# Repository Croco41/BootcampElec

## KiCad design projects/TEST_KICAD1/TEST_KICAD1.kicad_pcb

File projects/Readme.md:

# cgranja-piscineElec-design – Carte type Pro Mini (ATmega328P)

Petite carte basée sur un **ATmega328P-AU 16 MHz** 

---

## 1. Nomenclature (BOM)

| Référence | Qté | Valeur | Manufacture Part Number | Description | Caracteristiques | Empreinte |
| --- | --- | --- | --- | --- | --- | --- |
| C1,C2 | 2 | 12pF | CL10C120JB8NNNC | Unpolarized capacitor | 50V 12pF C0G ±5% 0603 Ceramic Capacitors RoHS | MyLibraryFootprint:MLF-CapacitorResistor-0603-1608mm |
| C3,C4,C5 | 3 | 100nF | CC0603KRX7R9BB104 | Unpolarized capacitor | 50V 100nF X7R ±10% 0603 Ceramic Capacitors RoHS | MyLibraryFootprint:MLF-CapacitorResistor-0603-1608mm |
| C6 | 1 | 1uF | CL10A105KB8NNNC | Unpolarized capacitor | 50V 1uF X5R ±10% 0603 Ceramic Capacitors RoHS | MyLibraryFootprint:MLF-CapacitorResistor-0603-1608mm |
| D1 | 1 | Green | TZ-P2-0603YGTCS1-0.6T | Light eminiting diode | 20mA 50mcd 570nm~575nm Yellow Green 1.9V~2.4V 60mW 0603 LED Indication - Discrete RoHS | MyLibraryFootprint:MLF-LED-0603-1608mm |
| D2 | 1 | Red | XL-1608SURC-06 | Light eminiting diode | 20mA 225mcd op View Mount 620nm~630nm Red 2.3V 50mW 0603 LED Indication - Discrete RoHS | MyLibraryFootprint:MLF-LED-0603-1608mm |
| J1 | 1 | ~ | | Header 1×12 (I/O) | | MyLibraryFootprint:MLF-J |
| J2 | 1 | ~ |  |Header 1×12 (I/O) | | MyLibraryFootprint:MLF-J2 |
| J3 | 1 | FTDI | | Header 1×6 (FTDI) | | MyLibraryFootprint:MLF-J3 |
| R1 | 1 | 33Ω | 0603WAF3300T5E |Resistor (LED SCK) | 100mW 330Ω 75V ±100ppm/℃ Thick Film Resistor ±1% 0603 Chip Resistor - Surface Mount RoHS | MyLibraryFootprint:MLF-CapacitorResistor-0603-1608mm |
| R2,R3 | 2 | 10K | RC0603FR-0710KL | Resistor (pull-up RST / DTR) | 100mW 10kΩ 75V ±100ppm/℃ Thick Film Resistor ±1% 0603 Chip Resistor - Surface Mount RoHS | MyLibraryFootprint:MLF-CapacitorResistor-0603-1608mm |
| SW1 | 1 | SW_Push | B3U-1000P | Bouton poussoir RESET | 12V 2.5mm Round Button 3mm SPST 50mA SMD,3x2.5mm Tactile Switches RoHS | MyLibraryFootprint:MLF-Switch_button_B3U-1000P |
| U1 | 1 | ATmega328P-A | ATMEGA328P-AU | MCU TQFP-32 16 MHz | AVR 20MHz 23 TQFP-32(7x7) Microcontrollers RoHS | MyLibraryFootprint:MLF-ATmega328P-AU-32Av3 |
| Y1 | 1 | 16MHz | X322516MLB4SI | Quartz 4 broches (GND sur 2 et 4) | Crystal Oscillator 9pF SMD3225-4P Crystals RoHS | MyLibraryFootprint:MLF-Crystal |

---

## 2. Brochage (pinout)

### 2.1 J3 – Connecteur FTDI (programmation série)

Connecteur 1×6, compatible FTDI standard Pro Mini. De **GND** vers **DTR** 
6. GND  
5. GND / CTS (suivant le module FTDI)  
4. VCC (5 V)  
3. RXI (vers D0 du µC)  
2. TXO (depuis D1 du µC)  
1. DTR (reset auto via condensateur vers RESET)

---

### 2.2 J2 – (alimentation / analog / SPI)

Connecteur 1×12, de haut en bas : 

1. **RAW** – entrée VIN non régulée (5–12 V)  
2. **GND** – masse  
3. **RST** – reset actif bas  
4. **VCC** – 5 V régulé  
5. **A3** – PC3 / ADC3  
6. **A2** – PC2 / ADC2  
7. **A1** – PC1 / ADC1  
8. **A0** – PC0 / ADC0  
9. **D13 / SCK** – PB5, SPI clock, LED verte D1  
10. **D12 / MISO** – PB4, SPI MISO  
11. **D11 / MOSI** – PB3, SPI MOSI  
12. **D10 / SS** – PB2, SPI SS / PWM

---

### 2.3 J2 – (UART / GPIO numériques)

Connecteur 1×12, de haut en bas :

12. **TXO / D1** – PD1, UART TX  
11. **RXI / D0** – PD0, UART RX  
10. **RST** – reset  
9. **GND** – masse  
8. **D2** – PD2, INT0  
7. **D3** – PD3, INT1 / PWM  
6. **D4** – PD4  
5. **D5** – PD5, PWM  
4. **D6** – PD6, PWM  
3. **D7** – PD7  
2. **D8** – PB0  
1. **D9** – PB1, PWM

Les entrées analogiques supplémentaires **A4–A7** sont connectées directement aux broches correspondantes du microcontrôleur (A4/A5 pour I²C, A6/A7 uniquement analogiques).

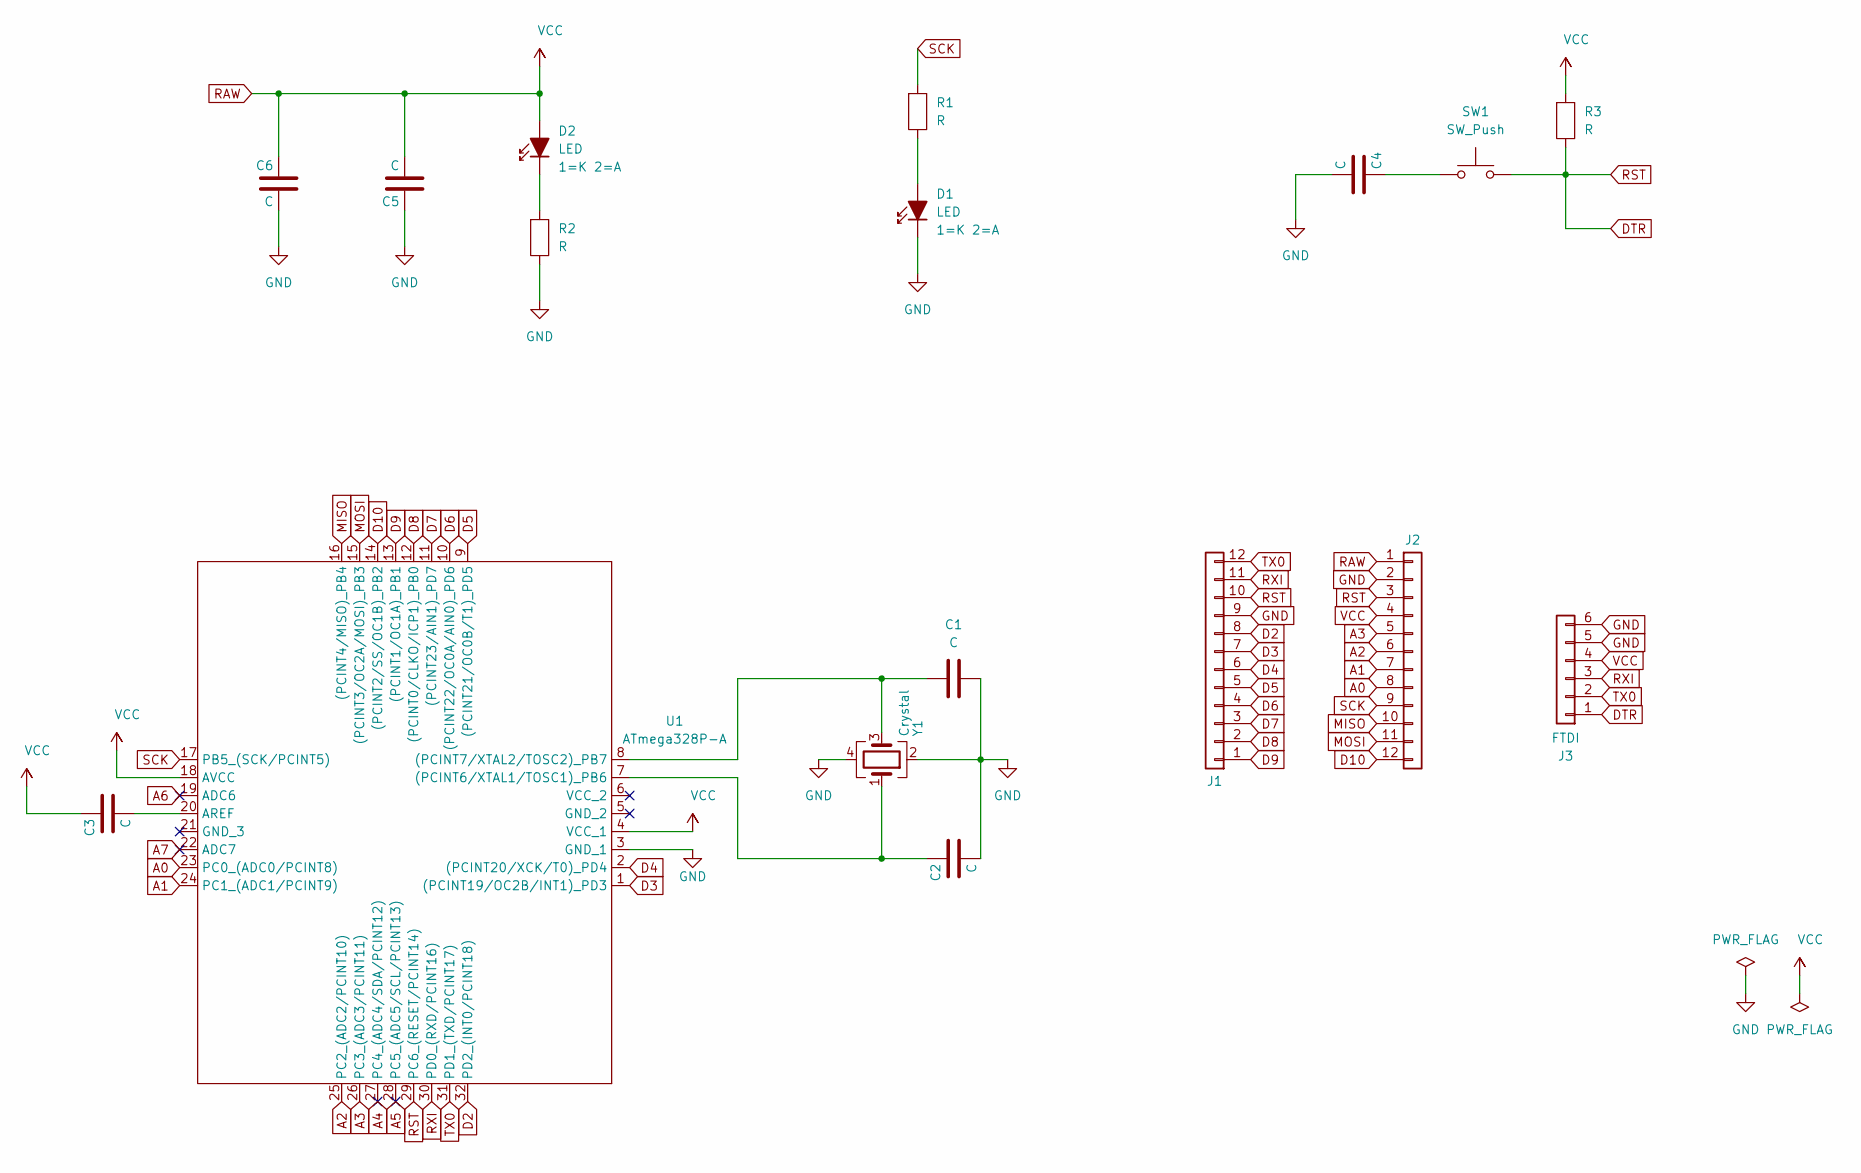
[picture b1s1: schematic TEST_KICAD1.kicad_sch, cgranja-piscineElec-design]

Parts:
C1, C2, C3, C4, C5, C6: C; MLF-CapacitorResistor-0603-1608mm
D1, D2: LED; MLF-LED-0603-1608mm
J1: MLF-J
J2: MLF-J2
J3: FTDI; MLF-J3
R1, R2, R3: R; MLF-CapacitorResistor-0603-1608mm
SW1: SW_Push; MLF-Switch_button_B3U-1000P; Manufacture Part Number B3U-1000P
U1: ATmega328P-A; MLF-ATmega328P-AU-32Av3
Y1: Crystal; MLF-Crystal

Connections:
A0: J2.8, U1.23 (PC0_(ADC0/PCINT8))
A1: J2.7, U1.24 (PC1_(ADC1/PCINT9))
A2: J2.6, U1.25 (PC2_(ADC2/PCINT10))
A3: J2.5, U1.26 (PC3_(ADC3/PCINT11))
A4: U1.27 (PC4_(ADC4/SDA/PCINT12))
A5: U1.28 (PC5_(ADC5/SCL/PCINT13))
A6: U1.19 (ADC6)
A7: U1.22 (ADC7)
D2: J1.8, U1.32 (PD2_(INT0/PCINT18))
D3: J1.7, U1.1 ((PCINT19/OC2B/INT1)_PD3)
D4: J1.6, U1.2 ((PCINT20/XCK/T0)_PD4)
D5: J1.5, U1.9 ((PCINT21/OC0B/T1)_PD5)
D6: J1.4, U1.10 ((PCINT22/OC0A/AIN0)_PD6)
D7: J1.3, U1.11 ((PCINT23/AIN1)_PD7)
D8: J1.2, U1.12 ((PCINT0/CLKO/ICP1)_PB0)
D9: J1.1, U1.13 ((PCINT1/OC1A)_PB1)
D10: J2.12, U1.14 ((PCINT2/SS/OC1B)_PB2)
DTR: J1.10, J2.3, J3.1, R3.2, SW1.1, U1.29 (PC6_(RESET/PCINT14))
GND: C1.2, C2.2, C4.2, C5.1, C6.2, D1.1 (K), J1.9, J2.2, J3.5, J3.6, R2.2, U1.3 (GND_1), Y1.2, Y1.4
MISO: J2.10, U1.16 ((PCINT4/MISO)_PB4)
MOSI: J2.11, U1.15 ((PCINT3/OC2A/MOSI)_PB3)
unnamed: C4.1, SW1.2
unnamed: D1.2 (A), R1.2
unnamed: D2.1 (K), R2.1
unnamed: C2.1, U1.7 ((PCINT6/XTAL1/TOSC1)_PB6), Y1.1
unnamed: C1.1, U1.8 ((PCINT7/XTAL2/TOSC2)_PB7), Y1.3
unnamed: C3.2, U1.20 (AREF)
RAW: C3.1, C5.2, C6.1, D2.2 (A), J2.1, J2.4, J3.4, R3.1, U1.4 (VCC_1), U1.18 (AVCC)
RXI: J1.11, J3.3, U1.30 (PD0_(RXD/PCINT16))
SCK: J2.9, R1.1, U1.17 (PB5_(SCK/PCINT5))
TX0: J1.12, J3.2, U1.31 (PD1_(TXD/PCINT17))

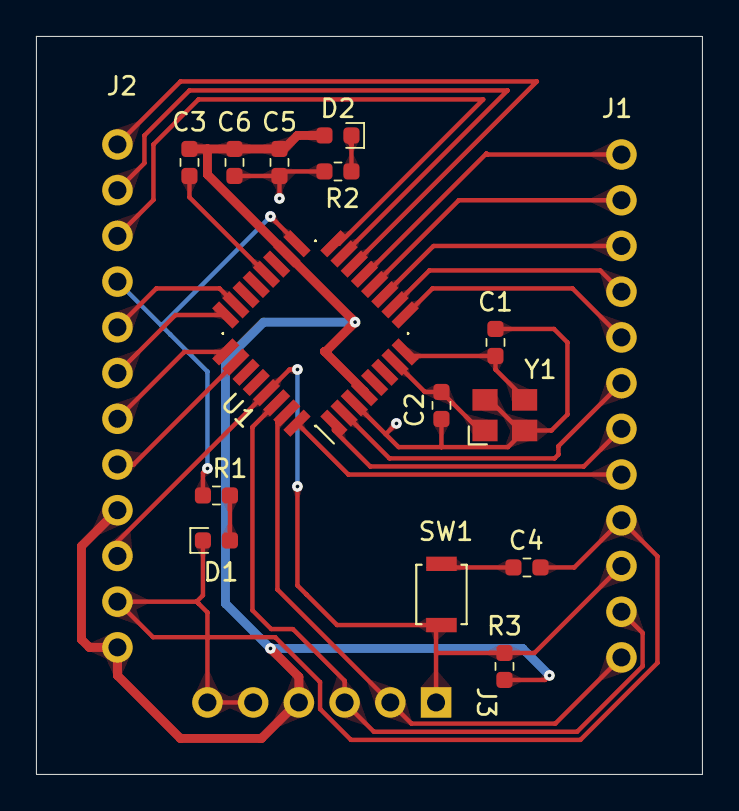
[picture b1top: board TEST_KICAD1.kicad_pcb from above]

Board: 2 copper layers, 37.0 x 41.0 mm, 17 parts (0 on the bottom side), 27 nets.

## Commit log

2025-11-19 working config for docker @42
2025-11-20 PROJET TEST_KICAD1 dans /projets avec les symboles de base + ATMega et debut schema
2025-11-20 creation schematics, ajout power_flag, premier test erc
2025-11-21 debut footprint
2025-11-21 fin footprint
2025-11-22 link footprint-symbol
2025-11-22 debut design pcb
2025-11-24 ajout PCB
2025-11-26 fin PCb, bom
